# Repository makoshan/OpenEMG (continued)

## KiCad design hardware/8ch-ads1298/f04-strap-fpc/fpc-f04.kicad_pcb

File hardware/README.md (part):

# OpenEMG 模块化硬件家族总览（2ch / 8ch / 16ch 共用主控与壳体）

**当前下单主板**　[OpenEMG MAIN V1.0B 定版](main-v1.0b/)（2026-11-24）。4 层，首批已下单，实物验证待完成。

**配套腕带**　[OpenEMG WB v0.1 八节电极表带](wb-v0.1/)已机械定版，提供可编辑模型、打印文件和逐缝弯曲检查，待首件实测。

> [!IMPORTANT]
> **人工审核准备下单 vs AI 生成未下单（下单前必读）**
> - **经人工硬件工程师设计并逐脚审核通过、准备下单的 v0.01 双板**：[`16ch-afe-hirose-1mm-1nf/`](16ch-afe-hirose-1mm-1nf/)（`OpenEMG v0.01` 双板：6 层 `C08B-U9` 主控板 + 带 32 路 `ESD401DPYR` 输入保护管的广濑 `1.0 mm` `1 nF` 4 层采集板，146 个贴片位号，已对照 TI `ADS1298` 数据手册与 `SBAU171D` 逐脚审核通过，准备打样做离体台架首测）。
> - **其余 AI 生成设计（尚未人工审核 · 尚未下单）**：除历史 8 路台架开发板 [`8ch-ads1298/r01-bench/`](8ch-ads1298/r01-bench/) 已做过离体实板测试外，以下历史设计——包括 `16ch-u9-dual30/`（`22 pF` 穿戴派生版）、`16ch-afe-xunpu-2mm-1nf/`、`16ch-c08b-round/`（双 34 针 `D20/R4U6`）、`8ch-ads1298/afe-d20*-8ch/`、`2ch-ads1292/`、全部柔性电极软板（FPC）及全部 3D 打印外壳——均为 AI 生成参考设计，**尚未经人工工程师逐板审核，也尚未下单打样**。

**AI 结构与叠板探索 · 新版 16 通道小型化派生双板（双 30P 四层软板 + `9.60 mm` 超薄圆润手表壳，DRC 0 / 飞线 0，AI 生成未下单）**　[U9 圆角 6 层 `0.80 mm` 双核主控 `OpenEMG-C08B-Mainboard-Rev0.01`、超薄双 30P 4 层 `0.80 mm` 采集板 `AFE-30P`、双 30P 四层保护软板 `strap-fpc-30p` 与圆润无外露螺丝手表壳 `enclosure-u9-watch`](16ch-u9-dual30/) 使用东侧 20 芯反序排线直连，已完成：① 主控 `Rev0.01` 恢复 `26.64 × 20.90 mm` 原矩形电池窗（东梁宽 `2.76 mm`）、同步 6 层 `0.80 mm` 真实叠层、去掉中央 `DEBUG` 线框并整洁重排丝印、32MHz 晶振泪滴与 `BUTTON_N` 飞线清零；② `AFE-30P` 升级 `1.00 mm` 超薄上下双触点 30P 座（`C324727`）、`43.10 × 36.50 mm` 四角 `R1.80` 圆角与 `0.80 mm` 四层板厚、`FPC2.17/18` 交叉修正、`ADS1298` `RESV1=GND` 修正、32 颗共模电容空贴 DNP（钢网 64 孔全剥离）+ 16 颗 `22 pF` 差分电容保 CMRR、`C10=1 µF` 飞跨电容、`Inner2` 北数字 `GND`/南模拟 `AGND` 分岛及晶振下完整参考地；③ 配套 `32×100 kΩ + 2×200 kΩ` 贴肤限流双 30P 四层软板及 `46.80 × 40.00 × 9.60 mm` 超薄圆润手表壳（最小壁厚 `0.85 mm`，23 对三维布尔 `0.000 mm³` 零干涉）。下文 `D20 / R4U6 / 8ch / 2ch` 属于双 34 针及入门参考系列，完整保留供对照复刻。

本目录收录 OpenEMG 全系硬件的 **KiCad 10 原生工程**、**嘉立创 EDA 专业版（`.epro2` / `.epcb2`）工程**、**生产制造包（Gerber / BOM / CPL / IPC-D-356，全系 17 套直接上传包清单与 SHA-256 核对见 [ORDER-MATRIX.md](ORDER-MATRIX.md)）** 与 **3D 打印圆润外壳（`build123d` Python + STEP/STL/GLB）**，统一按 **[CERN-OHL-S-2.0](../LICENSE-HARDWARE)** 强互惠开源硬件协议发布。

最新工程师版见 [U9 主控与 D2 双 34P 采集板开发稿](u9-d2/README.md)。采集板正在重布线。

### 三维光追渲染预览（[`renders/`](renders/)，基于源工程一键复现，非实物照片）

> **边界说明**：以下 8 组 16 张图片均为 Blender Cycles 光追设计预览（哑光黑阻焊 + `#c8964a` 沉金焊盘 + 工程高透壳示意），不代表制造或人体佩戴验收；套件收纳图为模块化开源复刻防静电 EVA 收纳示意，非商业零售包装。复现脚本见 [`renders/README.md`](renders/README.md)。

| 类别 | 正交俯视（Top） | 透视斜视（Iso） |
|---|---|---|
| **1 · 成品总览**<br>左：16ch `C08B R13` 整表正反双姿态<br>右：2ch `ADS1292 R7` 一体盒正反双姿态 |  |  |
| **2 · 开源复刻套件收纳示意**<br>`C08B` 胶囊 + `8ch/2ch` 可换采集板 + `P44e` + `34P` 软板 + `Pod D1` |  |  |
| **3 · 三档叠板立体爆炸组装图**<br>左 `16ch R13` · 中 `8ch D20-8CH` · 右 `2ch R7` |  |  |
| **4 · 柔性电极表带系统**<br>`16ch D2` A/B 软板 + `8ch D2-8CH` 单片软板 + `0.8 mm` TPU 定位层 + `F04` 连续表带 |  |  |
| **5 · 贴肤镀金干电极微距**<br>`2ch` 板底六触点 + 外扣六孔底盖 `Cap D2` + `Pod D1` 单豆分解与 16 节织带阵列 |  |  |
| **6 · C08B 双板与胶囊叠装总览**<br>左：采集板 `D20` · 中：主控 `R4U6` · 右：叠装透视 |  |  |
| **7 · 下板：采集板 `D20`** |  |  |
| **8 · 上板：共用主控 `R4U6`** |  |  |

---

## A · 为什么 2 / 8 / 16 通道能共用同一个主控板与外壳家族？

三档穿戴采集板均采用完全相同的 **`43.10 × 36.50 mm`** 四层板框包络（同时提供配四角螺丝柱外壳 `R12` 的**圆孔版 `R4U6 / D20 / D20-8CH`**，以及配无螺丝抱柱外壳 `R13` 的**四角缺口版 `R4U6N / D20N / D20N-8CH`**，同档位两版 BOM/CPL 与走线 100% 一致），并统一使用东南角的 **20P `0.5 mm` 下接 FPC 座（`FH34SRJ-20S-0.5SH(50)`，立创 `C2802370`，开口均朝南）** 进行上下叠板互联，由 `firmware/c08b-bringup` 上电免跳线自动识别 `2ch / 8ch / 16ch`：

| 主控 `J_AFE` 脚号 | 共用主控 `R4U6` 网名 | 对应采集端脚号 (`21-k`) | `16ch D20` 网名 | `8ch D20` 单面贴网名 | `2ch ADS1292` 网名 | 兼容性结论 |
|---:|---|---:|---|---|---|---|
| `1, 2` | `3V3_AFE` | `20, 19` | `3V3` | `3V3` | `3V3` | ✓ 3.3V 供电直通 |
| `3` | `NC` | `18` | `ADS_CLKSEL`（板内下拉） | `ADS_CLKSEL`（板内下拉） | `NC` | ✓ 无冲突 |
| `4` | `ADS_DRDY_A` (`PA2`) | `17` | `ADS_DRDY_A` | `ADS_DRDY_A` | `ADS_DRDY_N` | ✓ 主片中断对齐 |
| `5` | `AFE_GPIO3` (`PA0`) | `16` | `AFE_GPIO3` | `AFE_GPIO3` | `NC` | ✓ 无冲突 |
| `6` | `DOUT_B` (`SPI1_MISO`) | `15` | `DOUT_B` | `DOUT_B` | `ADS_DOUT` | ✓ MISO 对齐 |
| `7, 9, 20` | `GND`（`8` 悬空） | `14, 12, 1` | `GND` | `GND` | `GND`（`13` 亦地） | ✓ 多点地回流对齐 |
| `10` | `AFE_SCLK` (`SPI1_SCK`) | `11` | `SCLK_B` | `SCLK_B` | `MCU_SCLK` | ✓ SPI 时钟对齐 |
| `11` | `AFE_CS_A` (`PB0`) | `10` | `ADS_CS_A` | `ADS_CS_A` | `ADS_CS_N` | ✓ 主片选对齐 |
| `12` | `AFE_START` (`PA3`) | `9` | `ADS_START` | `ADS_START` | `ADS_START` | ✓ 硬件同步启动对齐 |
| `13` | `NC` | `8` | `AFE_CLK_IN`（板载晶振） | `AFE_CLK_IN`（板载晶振） | `NC`（内部时钟） | ✓ 无冲突 |
| `14` | `AFE_RESET` (`PA8`) | `7` | `ADS_RESET` | `ADS_RESET` | `NC` | ✓ `ADS1292` 复位并入 `PWDN` |
| `15` | `AFE_PWDN` (`PA1`) | `6` | `ADS_PWDN` | `ADS_PWDN` | `MCU_PWDN` | ✓ 硬件掉电/复位对齐 |
| `16` | `AFE_DIN` (`SPI1_MOSI`) | `5` | `DIN_B` | `DIN_B` | `ADS_DIN` | ✓ MOSI 对齐 |
| `17` | `AFE_CS_B` (`PB1`) | `4` | `ADS_CS_B` | 空贴 `V4_U2` | `NC` | ✓ 2ch/8ch 悬空安全 |
| `18` | `AFE_DRDY_B` (`PA4`) | `3` | `ADS_DRDY_B` | 空贴 `V4_U2` | `AVDD_SENSE`（串 `100kΩ`） | ✓ 16ch 从片中断 / 2ch 读 3.0V 模拟电 |
| `19` | `NC`（`P44e` 上为 `5V`） | `2` | `NC` | `NC` | `XIAO_5V`（`10kΩ` 下拉） | ✓ 接 `R4U6` 时由主控切断 `3V3_AFE` 互锁；接 `P44e` 时驱动 `Q1` 互锁 |

### 机械坐标对位说明（板中心 `(0, 0)` 口径）
- **主控 `R4U6` 底面 `J_AFE`**：焊盘中心群 `(+14.34, -10.50) mm`（排线插口基准 `-11.75 mm`）
- **`8ch / 16ch D20` 顶面 `J_AFE`**：焊盘中心群 `(+14.34, -10.50) mm`（插口基准 `-11.75 mm`，与 `R4U6` **`0.00 mm` 完全正对**，短 U 形排线直连）
- **`2ch ADS1292` 顶面 `J2`**：`(+12.00, -11.40) mm`（与入门上层板 `P44e` `0.00 mm` 正对；若改配 `R4U6` 主控叠装，横向仅偏 **`2.34 mm`**，选用约 `25 mm` 长的 0.5 mm 20P 软排线微斜过渡即可）。

---

## B · 嘉立创 EDA 专业版工程文件（`.epro2` / `.epcb2`）快速索引

直接在**嘉立创 EDA 专业版（客户端 V2.2+ / 网页版）**选择「文件 → 导入 → 嘉立创EDA专业版」即可打开带完整原理图、多层 PCB 与 3D 预览的工程：

| 档位与用途 | 工程文件路径 | 说明 |
|---|---|---|
| **16ch `v0.01` 双板合并工程 + 广濑 `1.0 mm` `1 nF` 台架采集板 + 配套表带软板（A5＋B1）** | `16ch-afe-hirose-1mm-1nf/OpenEMG_v0.01_DualBoard.epro2`<br>`16ch-afe-hirose-1mm-1nf/kicad/`<br>`16ch-afe-hirose-1mm-1nf/strap-fpc-a5b1/OpenEMG_v0.01_Strap_FPC_A5B1.epro2`<br>`16ch-afe-xunpu-2mm-1nf/AFE-30P.epro2` | **2026-11-15 人工工程师逐脚审核定版双板工程**，采集板 D101–D132 共 32 颗 ESD401、146 个贴片位号（`01 主控板` + `02 采集板` 四角 `R1.80` 圆角、现货 `0603 R4=104kΩ C861070`、广濑 `1.0 mm` 双 30P + `1 nF` 差分网络，含同步单板 Gerber/BOM/CPL 及 1:1 导出的 KiCad 8 原生双板与九页原理图 `kicad/`）；配套 `strap-fpc-a5b1/` 双层 30P 表带软板（盒底 A5＋B1 六柱，已投单待实物试装）；附 AI 派生讯普 `2.0 mm` 对照版（未下单） |
| **16ch 6 层圆角主控 `Rev0.01` + 超薄双 30P `22 pF` 穿戴派生版（AI 生成 · 未下单）** | `16ch-u9-dual30/OpenEMG-C08B-Mainboard-Rev0.01.epro2`<br>`16ch-u9-dual30/AFE-30P.epro2` | AI 结构与叠板派生参考：6 层 `OpenEMG-C08B-Mainboard-Rev0.01` + 4 层 `0.80 mm` 圆角 `R1.80` 超薄双 30P（`C324727`）`AFE-30P`（`22 pF` 差分网络，含 `fab-mcu-u9/`、`fab-afe-30p/` 与 KiCad 四层软板 `strap-fpc-30p/`，尚未人工审核、尚未下单） |
| **16ch 圆孔全套汇总（配 `R12` 壳）** | `16ch-c08b-round/jlc-eda/C08B-全套汇总-主控R4U6-采集D20.epro2` | 同时包含 `R4U6` 主控板、双面 `D20` 采集板与双软板原理图 + 四层 PCB |
| **16ch 缺口全套汇总（配 `R13` 壳）** | `16ch-c08b-round/jlc-eda/C08B-全套汇总-主控R4U6N-采集D20N.epro2` | 同时包含四角缺口主控 `R4U6N`、双面缺口采集板 `D20N` 与双软板原理图 + 四层 PCB |
| **16ch 采集板独立工程（圆孔 / 缺口）** | `16ch-c08b-round/jlc-eda/C08B-AFE采集板-D20-原理图+PCB+3D.epro2`<br>`16ch-c08b-round/jlc-eda/C08B-AFE采集板-D20N-缺口-原理图+PCB+3D.epro2` | 16ch 双面采集板单板工程（圆孔版与四角缺口版） |
| **8ch 纯单面圆孔全套汇总（配 `R12` 壳）** | `8ch-ads1298/afe-d20-8ch/jlc-eda/C08B-8ch全套汇总-主控R4U6-采集D20-8CH单面.epro2`<br>[11 页全套 PDF](8ch-ads1298/afe-d20-8ch/views/schematic.pdf) · [34P/20P 逐针核对表](8ch-ads1298/afe-d20-8ch/PINOUT-AND-REVIEW.md) | 同时包含 `R4U6` 主控、纯单面 `D20-8CH` 采集板与单片 4 层软板 `D2-8CH` + **11 页原理图（含 P1 整机框图、P2 电源树）** |
| **8ch 纯单面缺口全套汇总（配 `R13` 壳）** | `8ch-ads1298/afe-d20n-8ch/jlc-eda/C08B-8ch全套汇总-主控R4U6N-采集D20N-8CH单面.epro2` | 同时包含 `R4U6N` 缺口主控、纯单面缺口 `D20N-8CH` 采集板与单片软板 `D2-8CH` + 9 页原理图 |
| **8ch 纯单面采集板独立工程（圆孔 / 缺口）** | `8ch-ads1298/afe-d20-8ch/jlc-eda/C08B-AFE采集板-D20-8CH-单面8路-原理图+PCB+3D.epro2`<br>[6 页采集板 PDF](8ch-ads1298/afe-d20-8ch/views/afe-schematic.pdf)<br>`8ch-ads1298/afe-d20n-8ch/jlc-eda/C08B-AFE采集板-D20N-8CH-缺口单面8路-原理图+PCB+3D.epro2` | 纯单面 8 路采集板（正面 76 颗贴片，背面 0 器件绿油绝缘；圆孔版含 **6 页原理图**与[排线朝向图](8ch-ads1298/afe-d20-8ch/views/d20-8ch-wiring-orientation.svg)） |
| **8ch 单片 4 层表带软板 `D2-8CH`** | `8ch-ads1298/strap-fpc-d2-8ch/jlc-eda/C08B-表带软板-D2-8CH单片.epro2` | 单片 4 层 34P 软板（胶囊底双辅助 `200k` 串阻 + 6 窗 `0.20 mm` PI 垫片复用现成底盖） |
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
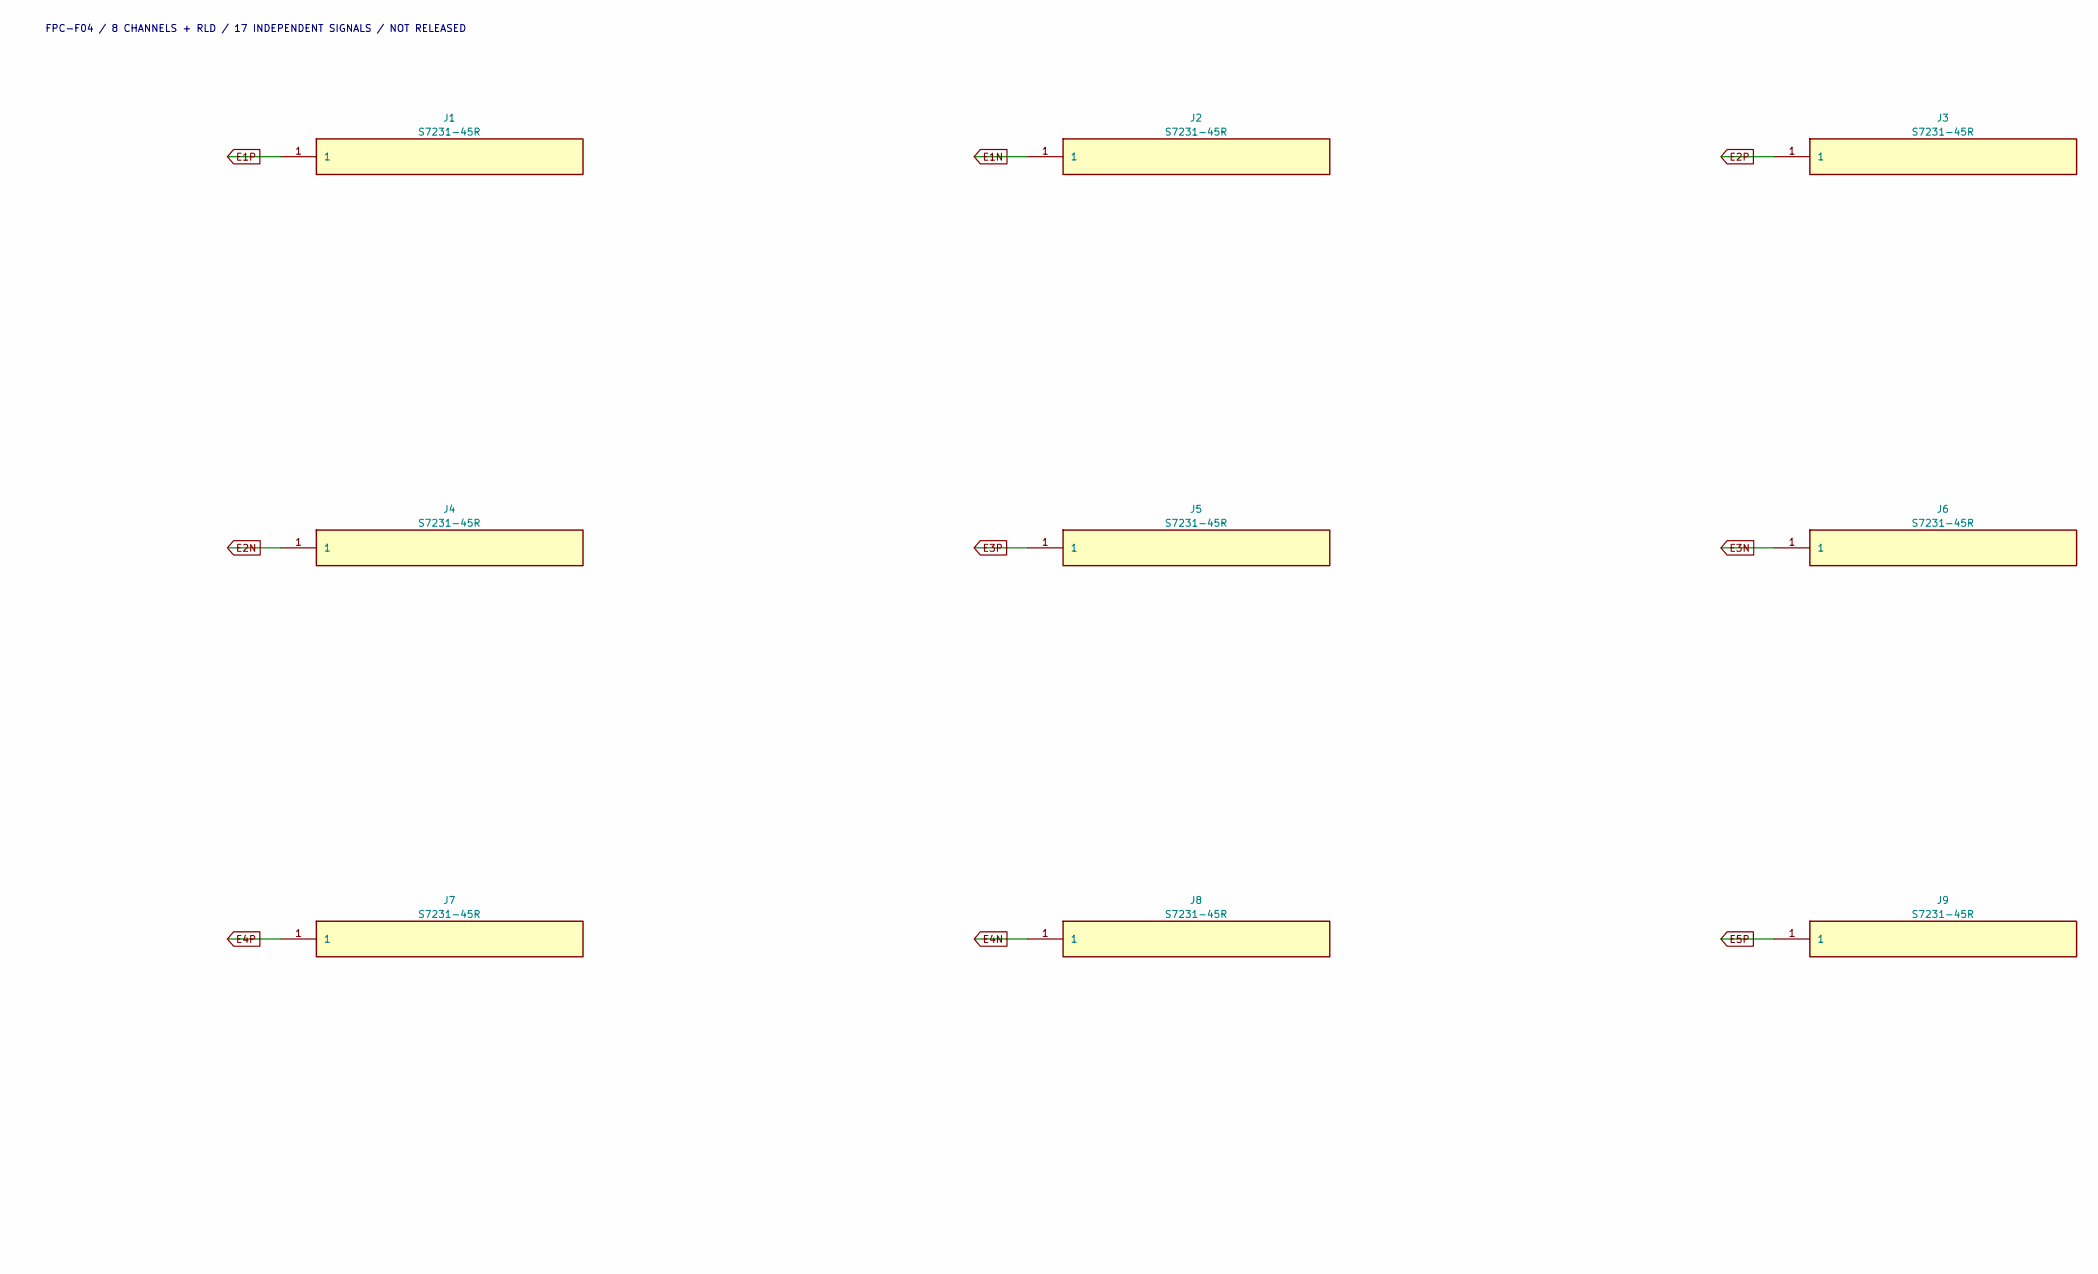
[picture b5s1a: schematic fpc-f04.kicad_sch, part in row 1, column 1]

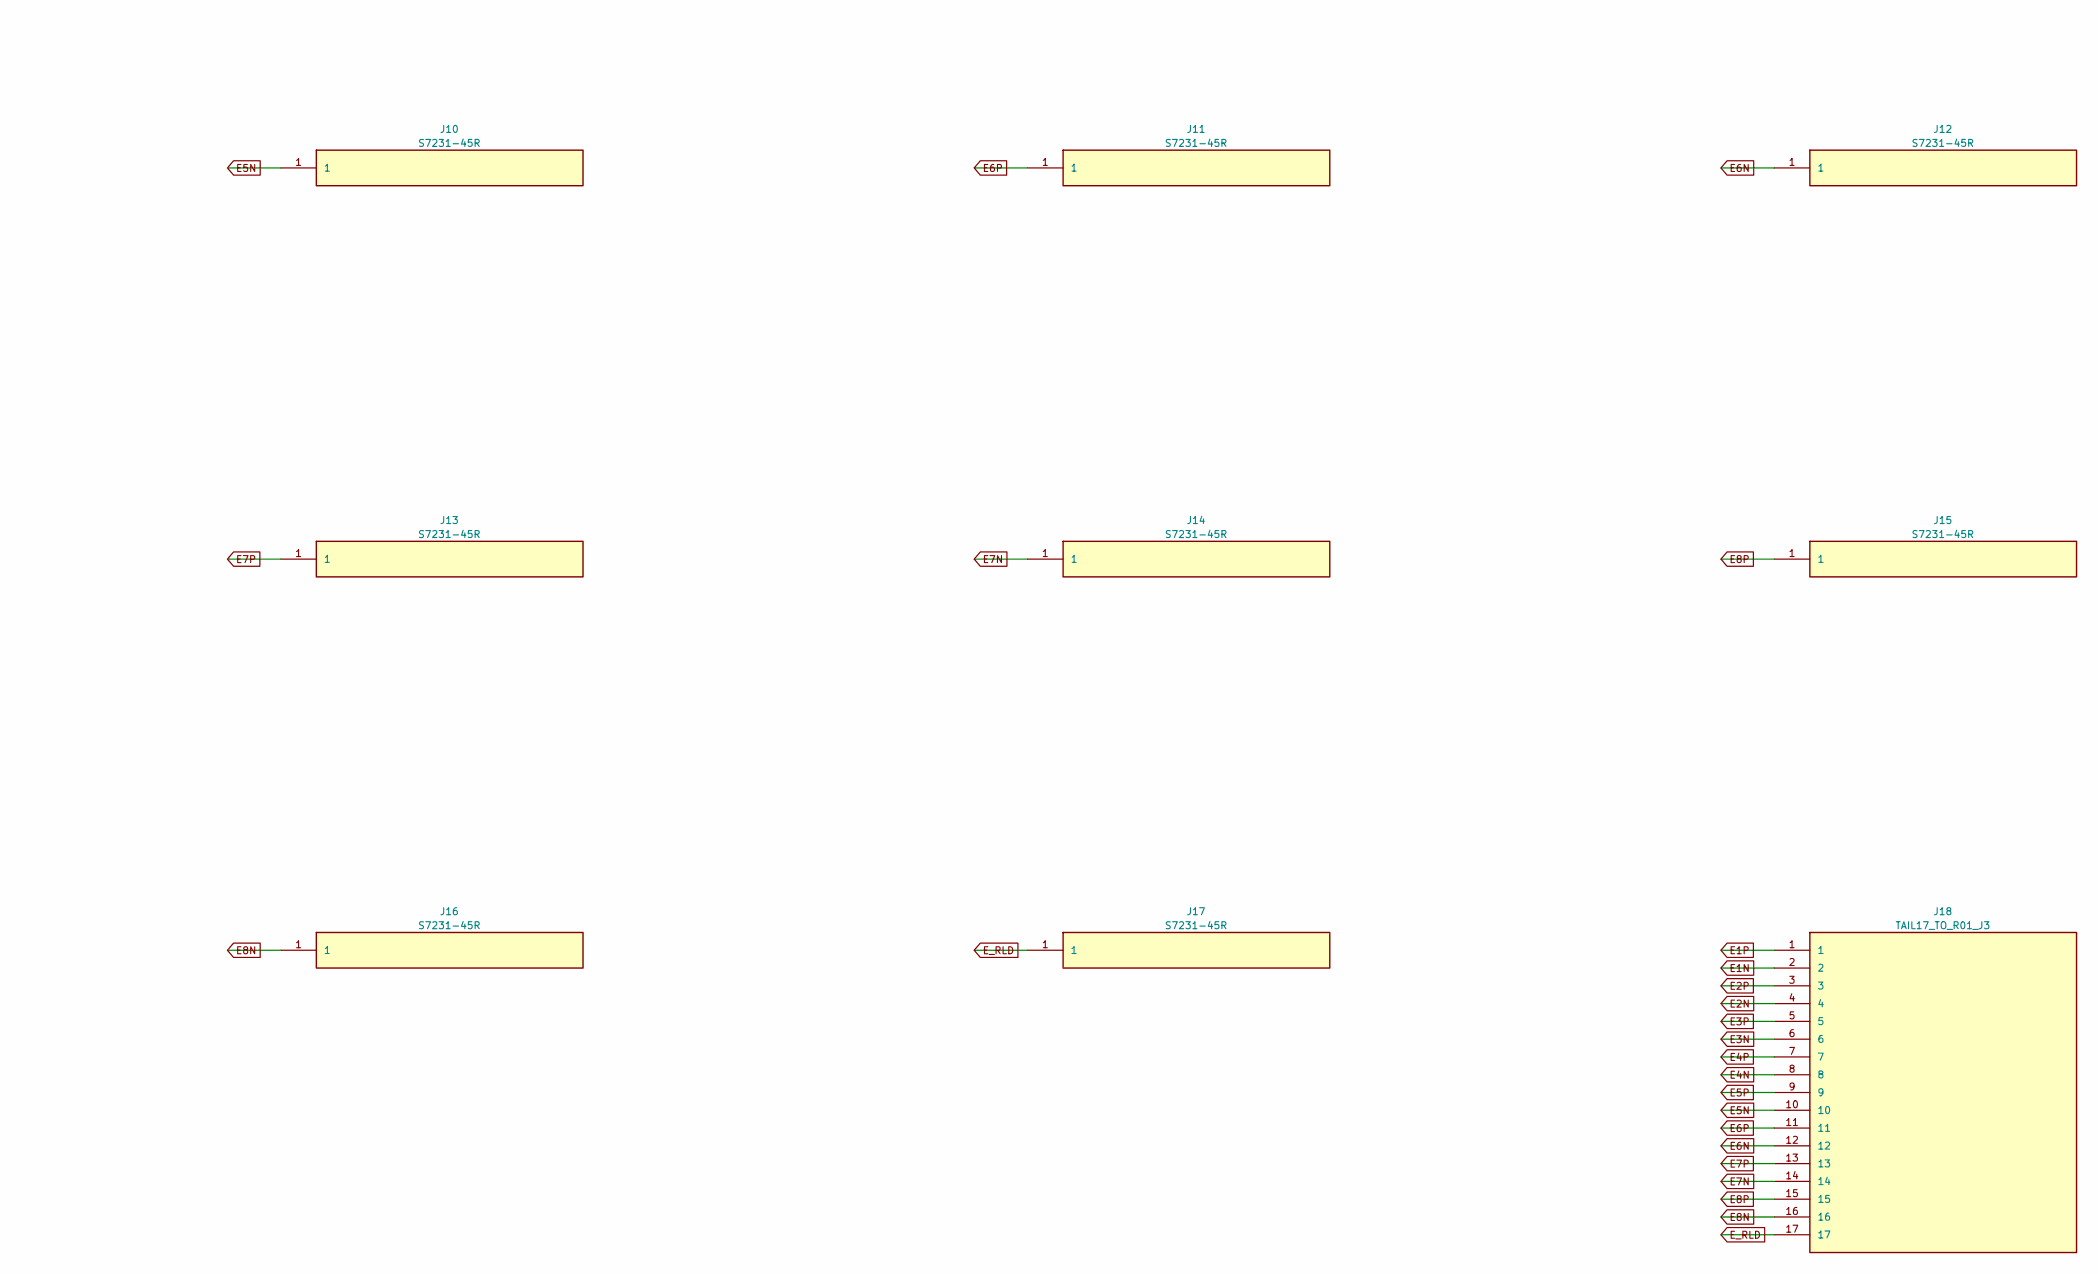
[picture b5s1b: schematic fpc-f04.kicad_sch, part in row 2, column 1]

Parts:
J1, J2, J3, J4, J5, J6, J7, J8, J9, J10, J11, J12, J13, J14, J15, J16, J17: S7231-45R; S7231
J18: TAIL17_TO_R01_J3; TAIL17

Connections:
E1N: J2.1, J18.2
E1P: J1.1, J18.1
E2N: J4.1, J18.4
E2P: J3.1, J18.3
E3N: J6.1, J18.6
E3P: J5.1, J18.5
E4N: J8.1, J18.8
E4P: J7.1, J18.7
E5N: J10.1, J18.10
E5P: J9.1, J18.9
E6N: J12.1, J18.12
E6P: J11.1, J18.11
E7N: J14.1, J18.14
E7P: J13.1, J18.13
E8N: J16.1, J18.16
E8P: J15.1, J18.15
E_RLD: J17.1, J18.17

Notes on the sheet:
FPC-F04 / 8 CHANNELS + RLD / 17 INDEPENDENT SIGNALS / NOT RELEASED

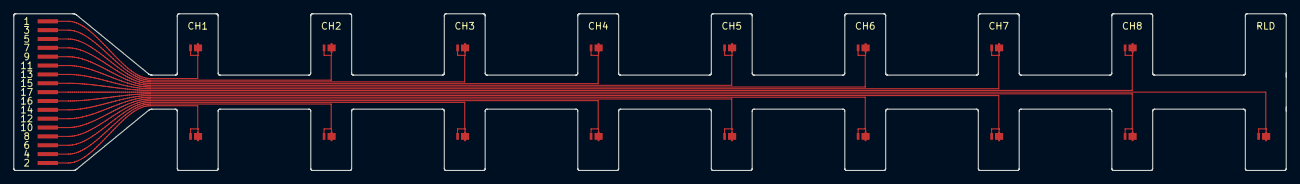
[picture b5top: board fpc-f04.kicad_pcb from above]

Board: 2 copper layers, 186.8 x 23.0 mm, 18 parts (0 on the bottom side), 17 nets.

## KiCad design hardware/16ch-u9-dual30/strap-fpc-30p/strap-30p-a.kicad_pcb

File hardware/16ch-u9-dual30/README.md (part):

# 16 通道小型化旗舰：U9 圆角 6 层主控（`Rev0.01`）+ 超薄双 30 针采集板 + 四层保护软板 + 超薄圆润手表壳（2026-11-14 开源定版）

本目录收录 `OpenEMG-C08B-Mainboard-Rev0.01`（6 层 `0.80 mm` 圆角双核主控，原矩形 `26.64 × 20.90 mm` 电池窗、去中央 DEBUG 框洁净丝印版）与 `AFE-30P`（4 层 `0.80 mm` 圆角超薄双 30 针 16 路采集板）配对工程、嘉立创直接上传制造包（单板与 `70.20 × 70.20 mm` 工艺边 Gerber、SMT BOM、192 颗逐脚拟合校核 CPL、极性图）、满载器件整板 STEP、双 30P 四层保护表带软板（`strap-fpc-30p/`）以及 `9.60 mm` 超薄圆润无外露螺丝手表壳（`enclosure-u9-watch/`，同时保留台架候选壳 `case-30p/`），按 [CERN-OHL-S-2.0](../../LICENSE-HARDWARE) 发布。

## 文件清单

| 路径 | 说明 |
|---|---|
| `OpenEMG-C08B-Mainboard-Rev0.01.epro2` / `mcu-u9-3d.step` | 6 层 `0.80 mm` 主控板（`STM32L432KCU6` `U7` + `nRF52840-QFAA` `U8`，`43.10 × 36.50 mm` 四角 `R=1.80 mm` + `26.64 × 20.90 mm` 原矩形电池开窗 + 去中央 DEBUG 框洁净丝印）及满载 588 实体 STEP |
| `AFE-30P.epro` / `AFE-30P.epro2` / `afe-30p-3d.step` | 4 层 `0.80 mm` 16 路圆角采集板（双 `ADS1298IPAGR` `U1/U2` + 双 `1.00 mm` 超薄上下双面触点 30P 座 `FPC1/FPC3` `C324727` + 20P 双面触点座 `FPC2` `Molex 503480-2000`）及满载 306 实体 STEP（已剔除 32 颗 DNP 共模电容占位块） |
| `20针接口.csv` | `MCU-U9 FPC1`（1..20）↔ `AFE-30P FPC2`（20..1）逐脚网络锁定表 |
| `fab-mcu-u9/OpenEMG-C08B-Mainboard-Rev0.01-Gerber.zip` | 主控 `Rev0.01` 6 层单板 Gerber（`GTL, G1..G4, GBL` + `GKO` + `PTH/NPTH`，已剔除 14 处手焊/DNP 钢网开窗，无中央 DEBUG 线框） |
| `fab-mcu-u9/OpenEMG-C08B-Mainboard-Rev0.01-panel702-Gerber.zip` | 主控 `Rev0.01` 自带 `70.20 × 70.20 mm` 工艺边（`2.0 mm` 铣槽 + 四边断口连接筋）一拼一 Gerber |
| `fab-mcu-u9/jlc_smt_bom.csv` / `jlc_smt_cpl.csv` | 主控 `Rev0.01` 嘉立创 SMT 物料清单与贴片坐标（45 种 / 110 颗：Top 42 + Bottom 68，按平台默认「AD 等其他」逐脚拟合） |
| `fab-mcu-u9/orientation.csv` / `polarity-*.png` | 主控 `Rev0.01` 有极性/多引脚器件 1 脚与阴极坐标核对表及顶/底层粉点核对图 |
| `fab-afe-30p/Gerber_AFE-30P.zip` | `AFE-30P` 4 层 `0.80 mm` `R=1.80 mm` 圆角单板 Gerber（`GTL, G1, G2, GBL` + `GKO` + `PTH`；`GTP/GBP` 已剥离全部 32 颗 DNP 共模电容共 64 个钢网开孔） |
| `fab-afe-30p/Gerber_AFE-30P-panel702.zip` | `AFE-30P` 自带 `70.20 × 70.20 mm` 工艺边（同心 `R1.80/R3.80` 圆角 `2.0 mm` 铣槽 + 6 处断口连接筋，完全避开南侧双 30P 与东侧 20P 插口）一拼一 Gerber |
| `fab-afe-30p/jlc_smt_bom.csv` / `jlc_smt_cpl.csv` | `AFE-30P` 嘉立创 SMT 物料清单与贴片坐标（22 种 / 82 颗：Top 48 + Bottom 34，100% 现货 `C` 料号，含 `C324727`、`R4=C2984407`、`C10=C52923` 1µF 与 16×`22pF` `C76924`，按平台默认「AD 等其他」逐脚拟合） |
| `fab-afe-30p/orientation.csv` / `polarity-*.png` | `AFE-30P` 有极性/多引脚器件 1 脚与阴极坐标核对表及顶/底层粉点核对图 |
| `strap-fpc-30p/` | 适配 `FPC1/FPC3` 横向错位 `1.524 mm` 的 **12+2+2 双极四层柔性表带软板**（`strap-30p-a` + `strap-30p-b`）：自带 `32 × 100 kΩ`（`C25741`）采样限流串阻与 `2 × 200 kΩ`（`C25811`）偏置串阻（叠加板上 `15 kΩ` / `392 kΩ` 后总串联阻抗 `115 kΩ` / `592 kΩ`），含 28 项门禁 `check.py`、满载 3D STEP 与 `fab/` 生产包 |
| `enclosure-u9-watch/` | **穿戴主力超薄圆润无外露螺丝手表壳**（主体净高 **`46.80 × 40.00 × 9.60 mm`**，`≤ 9.70 mm`；含外扣底盖不计铜凸 `10.806 mm`，含 `1.20 mm` 电极尖端总包络 `12.006 mm`；全壳最小壁厚 **`0.85 mm ≥ 0.80 mm`**）：内柱盲孔 `4 × M1.4` 紧固 + `cap_bottom` 卡扣遮蔽，经 `fit_3d_check.py` 核验满载双板/电芯/双软板共 **23 对三维布尔交叠 `0.000 mm³`** 及 9 项正反例对照 |
| `case-30p/` | 离体台架候选盒总装 STEP（`Case.step`、`Lid.step`、`assembly.step`）、`19.67 × 26.59 × 2.78 mm` 电芯干涉报告 `checks.json` 与装配图 |
| `verify_interface.py` / `SHA256SUMS` | 20P 逐脚对账、双核 39 信号脚固件兼容、60 脚双 30P 映射、双板 `0.80 mm` 叠层、前端 RC/电荷泵修正与 0/64 DNP 钢网零残留、192 颗 CPL 逐脚拟合（含 4 项必败反例）、铺铜与全套 3D 总装自检脚本及 SHA-256 校验表 |

## 已修复的工程与制造问题（嘉立创 EDA 专业版 `4.1.93` 原生复核通过）

### 1. 主控板 `OpenEMG-C08B-Mainboard-Rev0.01`（6 层 `0.80 mm`，`43.10 × 36.50 mm`）
- **定版原矩形电池镂空窗、东梁强度恢复与 `0.80 mm` 真实叠层同步**：电池开窗 `a6b31685508e342e` 采用无阶梯纯矩形 **`26.638 × 20.900 mm`**（东侧梁宽恢复至 **`2.762 mm`**，完美容纳标准 `302025` 锂电池且与 `SCREW3` 孔留足边距），同步对齐 `Inner3/Inner4` 内电层镂空框并重铺全部 10 块铜皮（`10 POUR / 24 POURED`）；`LAYER_PHYS` 同步为真实 6 层 `0.80 mm`（`JLC06081H-3313`，`31.321 mil = 0.7956 mm`），导出 588 实体 `mcu-u9-3d.step` 使整表壳体净高降至 **`9.60 mm`**。
- **四角 `R=1.80 mm` 圆角板框、北边拉平与洁净丝印**：消除原版北边 `0.166 mm` 倾斜，统一四角圆弧与内电层退缩外框；板面升级 `OpenEMG 0.01` 标识、去掉顶面中央 `DEBUG` 线框并双列对齐背面位号丝印。
- **消除全部网络飞线与孤立铜皮**：将 `BUTTON_N` 走线 `aa2a5e4ee3874f57` 延伸至 `SW300.1` 焊盘中心 `324.087 mil`，移除 2 处孤立泪滴，西南角地过孔 `cc7fc0d843f8c411` 内移至 `-1303 mil`；原生 DRC **0 间距/几何/连接错误、0 飞线**。
- **原理图与 PCB 充电芯片同步**：`U17` 统一为 `LTC4054ES5-4.2#TRPBF`（`SOT-23-5`，立创 `C462648`）。
- **钢网防连锡处理**：单板与 `70.2 × 70.2 mm` 工艺边 Gerber 已自动剔除 `J301`、`JP701`、`D62`、`BT1`、`ANT1` 等 14 处手焊/空贴焊盘钢网开孔。

### 2. 采集板 `AFE-30P`（4 层 `0.80 mm`，`43.100 × 36.500 mm` 四角 `R=1.80 mm`）
- **小型化机械与超薄双触点连接器升级**：板框收为与主控同心的 **`43.100 × 36.500 mm` 四角 `R=1.800 mm` 圆角板框**，四层叠层设为 **`0.80 mm`（`JLC04081H-3313`）**；正反双面 30P 表带座 `FPC1 / FPC3` 由 `2.00 mm` 高下接座升级为 **`1.00 mm` 超薄上下双面触点广濑 `FH34SRJ-30S-0.5SH(50)`（立创 `C324727`）**（无需区分上下接金手指面）。
- **前端高阻干电极 RC 滤波修正（消除工频共模转差模与肌电通带衰减）**：配合四层软板 `strap-fpc-30p` 的 `100 kΩ` 贴肤限流电阻（每脚总串联电阻 `R_leg = 115 kΩ`），将 32 颗对地共模电容（`C55, C57..C71, C93..C108`）全部设为 **空贴 DNP** 并在单板/拼板 Gerber `GTP/GBP` 钢网中 100% 剥离其 64 个焊盘开孔（避免 `±5%` 容差把 50 Hz 共模干扰直接转成差模底噪，并将原 `115 kΩ × 564 pF → f_c = 2.45 kHz` 误削肌电高频的问题彻底修正），同时将 16 颗跨通道差分电容（`C72..C79, C109..C116`）由 `47 pF` 调整为 **`22 pF C0G`（`GRM0335C1H220JA01D`，立创 `C76924`）**，精确锁定纯差模抗混叠截止频率 $f_{c,\text{diff}} = \frac{1}{2\pi \cdot 230\,\text{k}\Omega \cdot 22\,\text{pF}} = 31.45\,\text{kHz}$。
- **`LM27762` 负压电荷泵飞跨电容修正**：依 TI `LM27762` 手册 §8.2.1.2.3 要求，将飞跨电容 `C10` 由 `10 µF` 修正为 **`1 µF X5R 0402`（`CL05A105KA5NQNC`，立创 `C52923`）**，消除启动浪涌电流与电荷泵开关纹波超标隐患。
- **20P 反序排线 `FPC2.17 / 18` 交叉修复**：`FPC2` 第 17 脚改接 `CS#2`（`U2.39`，对主控 `FPC1.4，AFE_CS_B`），第 18 脚改接 `DRDY2#`（`U2.47`，对主控 `FPC1.3，AFE_DRDY_B`），过孔 `e1998` 移至 `(1305, 792.3834) mil`。
- **双 `ADS1298` 第 31 脚 `RESV1` 修正为数字地 `GND`**：依 TI `ADS1298` 数据手册（`RESV1` 必须接 `DGND`），将原理图（`1.esch` `e95/e300`）与 PCB（`U1.31`、`U2.31` 及相连过孔/短线）从 `AGND` 改为 `GND`，消除原理图与 PCB 网表差异（`0 Netlist Error`）。
- **`Inner2` 北数字 `GND` / 南模拟 `AGND` 分岛与晶振完整参考地**：将 `Inner2`（`layer 16`）拆分为北侧数字区 `POUR e1678 (GND)` 与南侧模拟电极区 `POUR e1687 (AGND)`（避免数字返回电流耦合进高阻电极扇出区），移除 `2.048 MHz` 晶振 `X1` 正下方的禁止铺铜框 `REGION e1680` 为时钟提供完整 `GND` 参考平面，保留 `RULE 7` 直连（`connType=1`），并在 `LCEDA-Pro 4.1.93` 重建全部 15 块铺铜；原生 DRC **0 错误、0 飞线、0 网表不一致**。
- **补齐全部 SMT 立创现货料号**：补齐 `C1, C2`（`22uF` `0402` `C105226`）、`C4, C34`（`10uF` `0402` `C7472949`）并将负轨反馈电阻 `R4` 更新为现货 `105 kΩ ±0.1%`（`C2984407`），整板 22 种 / 82 颗贴片件 100% 具备有效现货 `C` 料号。

### 3. 嘉立创 SMT 贴片坐标（`jlc_smt_cpl.csv`）极性与背面镜像修正
- 嘉立创 SMT 下单页默认选中 **「AD,99SE,Allegro,PADS(宏)等其他」**（背面按封装先 `X` 取反再旋转 `Rotation` 角），而嘉立创 EDA 内部 `COMPONENT` 背面按 `Y` 取反旋转，二者在背面相差 **`180°`**。
- `fab-mcu-u9/jlc_smt_cpl.csv`（110 颗）与 `fab-afe-30p/jlc_smt_cpl.csv`（82 颗）共 **192 颗**贴片件已统一修正为嘉立创默认上传模式（顶层保持原角，底层加 `180°`），经 `verify_interface.py` 逐脚拟合校验（最大焊盘偏差 **`0.0000 mm`**；`U17`、`FPC1`、`U2`、`FPC3` 减回 `180°` 反例均报 `> 1.5 mm` 错位拦截）。
- **下单必读**：上传 `jlc_smt_cpl.csv` 时**保持平台默认的「AD,99SE,Allegro,PADS(宏)等其他」选项，切勿改选「嘉立创EDA」**；在 2D 预览页同时勾选顶层与底层，对照 `orientation.csv` 及 `polarity-top.png` / `polarity-bottom.png` 核对粉点。

## 20 芯反序排线与三维 U 形装配关系（含防混插短路告警）

- 电气映射：主控 `FPC1` 的第 $k$ 脚接采集板 `FPC2` 的第 $21-k$ 脚。主控 `19、20` 脚为受控 `3V3_AFE`，接采集板 `2、1` 脚（`+3.3V`）；主控第 `1` 脚为 `GND`，接采集板第 `20` 脚（`GND`）。完整逐脚映射见 [20 针接口表](20针接口.csv)。
- 三维叠板走线：主控 `Rev0.01` 底面 `FPC1`（开口朝东，第 `1` 脚在北、第 `20` 脚在南）与下层 `AFE-30P` 顶面 `FPC2`（开口朝东，第 `20` 脚在北、第 `1` 脚在南）均为 `Molex 503480-2000` 上下双面触点座且南北物理对齐；使用 **20 芯 `0.5 mm` A 型（同面）软排线**向外平折 U 形直插即可自然实现 `k ↔ 21−k` 连接。
- **严禁跨系列混插警告**：`OpenEMG-C08B-Mainboard-Rev0.01`（东侧 `FPC1.1=GND, 19/20=3V3_AFE`）**仅限与 `AFE-30P` 互连**；切勿与 `R4U6 / D20 / D20-8CH / ADS1292-2ch` 系列（南侧 `J_AFE.1/2=3V3_AFE, 20=GND`）混插 20P 排线，亦严禁台架 `1 ↔ 1` 直连，否则上电瞬间 `3V3_AFE` 直接对 `GND` 短路。

## 固件二进制兼容与烧录路径

主控 `Rev0.01` 的双核信号脚（`U7 STM32L432KCU6` 23+3 脚 + `U8 nRF52840-QFAA` 16 脚，由 `verify_interface.py`、`c08b-bringup/tools/pins_u9.py` 与 `c08b-stream/tools/pins.py --check-u9` 三重自动断言）可直接运行免改动的 [`firmware/c08b-bringup`](../../firmware/c08b-bringup/README.md) 与 [`firmware/c08b-stream`](../../firmware/c08b-stream/README.md) 固件镜像：其中运行信号脚分配与 `R4U6 / R4U6N` 完全一致，仅 `U7.31`（`PH3-BOOT0`）接 `L_BOOT0`（经 `R5` `10 kΩ` 下拉至 `GND`，固件配置为无上下拉高阻输入，`L432` 侧 `l432_vbus_present()` 恒读 `0`；USB 电气安全互锁由硬件 `VBUS → R703/R704 → Q3 → U4 → OE_N` 切断隔离器以及 `nRF52840` 侧 `U8.3 P0.01=VBUS_SENSE` / `U8.15 P0.17=OE_N` 完整执行，自检与采集流均正常通过）：
1. **`nRF52840`（`U8`）**：通过顶面 `J301` 焊盘（`SWDIO / SWDCLK / GND / 3V3`）经 SWD 探针烧写 `nrf.hex` / `nrf_s140.hex`。
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
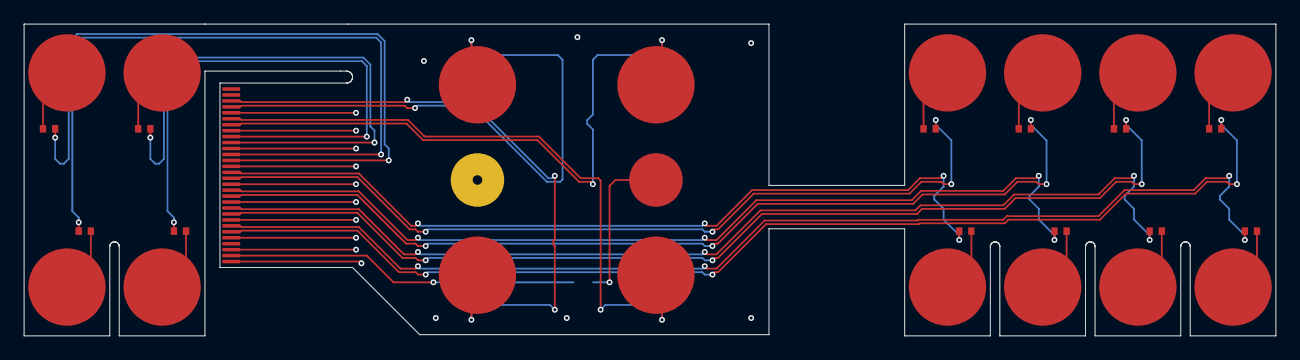
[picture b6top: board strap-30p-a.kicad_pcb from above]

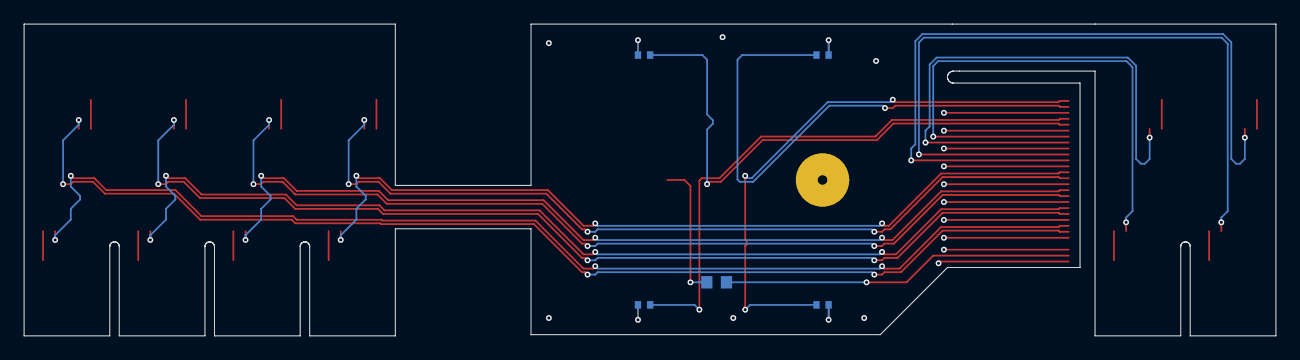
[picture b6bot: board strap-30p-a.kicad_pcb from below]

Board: 4 copper layers, 105.2 x 26.2 mm, 36 parts (5 on the bottom side), 35 nets.

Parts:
E1N, E1P, E2N, E2P, E3N, E3P, E4N, E4P, E5N, E5P, E6N, E6P, E7N, E7P, E8N, E8P: 贴肤焊盘（焊 Φ6×2.0 镀金铜片）; CONTACT_SMD_D6.5
EB1: 贴肤焊盘（焊方形 3×3×2 镀金铜片）; CONTACT_SMD_D6.5
EB2A: REF 贴肤焊盘（焊方形 3×3×2，孔内灌锡对焊 B 片 EB2）; CONTACT_D1.8
R1, R2, R3, R4, R5, R6, R7, R8, R9, R10, R11, R12, R13, R14, R15, R16: 100k; R0402
R33: 200k; R0603
TAIL_A: AFE-30P FPC1; FPC30_P0.5_TAIL

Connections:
AGND: TAIL_A.5, TAIL_A.8, TAIL_A.11, TAIL_A.14, TAIL_A.17, TAIL_A.20, TAIL_A.23, TAIL_A.26, TAIL_A.28, TAIL_A.30
BIAS_DRV1: R33.1, TAIL_A.29
BIAS_DRV1_E: EB1.1, R33.2
CH1_N: R2.1, TAIL_A.4
CH1_N_E: E1N.1, R2.2
CH1_P: R1.1, TAIL_A.3
CH1_P_E: E1P.1, R1.2
CH2_N: R4.1, TAIL_A.7
CH2_N_E: E2N.1, R4.2
CH2_P: R3.1, TAIL_A.6
CH2_P_E: E2P.1, R3.2
CH3_N: R6.1, TAIL_A.10
CH3_N_E: E3N.1, R6.2
CH3_P: R5.1, TAIL_A.9
CH3_P_E: E3P.1, R5.2
CH4_N: R8.1, TAIL_A.13
CH4_N_E: E4N.1, R8.2
CH4_P: R7.1, TAIL_A.12
CH4_P_E: E4P.1, R7.2
CH5_N: R10.1, TAIL_A.16
CH5_N_E: E5N.1, R10.2
CH5_P: R9.1, TAIL_A.15
CH5_P_E: E5P.1, R9.2
CH6_N: R12.1, TAIL_A.19
CH6_N_E: E6N.1, R12.2
CH6_P: R11.1, TAIL_A.18
CH6_P_E: E6P.1, R11.2
CH7_N: R14.1, TAIL_A.22
CH7_N_E: E7N.1, R14.2
CH7_P: R13.1, TAIL_A.21
CH7_P_E: E7P.1, R13.2
CH8_N: R16.1, TAIL_A.25
CH8_N_E: E8N.1, R16.2
CH8_P: R15.1, TAIL_A.24
CH8_P_E: E8P.1, R15.2

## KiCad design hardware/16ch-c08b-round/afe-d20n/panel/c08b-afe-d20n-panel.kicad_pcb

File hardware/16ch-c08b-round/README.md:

# 16 通道旗舰圆角上下叠板（`16ch-c08b-round`）

上层配共用主控 [`../common-mainboard/mainboard-r4u6/`](../common-mainboard/mainboard-r4u6/)（圆孔）或 [`../common-mainboard/mainboard-r4u6n/`](../common-mainboard/mainboard-r4u6n/)（四角缺口），下层为本目录的双面双 `ADS1298` 16 通道采集板 `afe-d20/`（圆孔）或 `afe-d20n/`（四角缺口），外接 34P 四层柔性表带软板，分别装入 [`../enclosure-46x40/c08b-shell-r12/`](../enclosure-46x40/c08b-shell-r12/)（螺丝壳）或 [`../enclosure-46x40/c08b-shell-r13-notch/`](../enclosure-46x40/c08b-shell-r13-notch/)（无螺丝抱柱壳）。

| 采集板 `D20` 正交俯视（渲染预览） | 采集板 `D20` 透视斜视（渲染预览） |
|---|---|
|  |  |

| 34P 双片柔性软板与 `0.8 mm` TPU 定位层（三维光追设计预览，非实物照片，不代表制造或人体佩戴验收通过） | 外扣六孔底盖与 `Pod D1` 穿带式双极干电极（三维光追设计预览，非实物照片，不代表制造或人体佩戴验收通过） |
|---|---|
|  |  |

## 目录结构

- `afe-d20/`：**圆孔版（配 `R12` 螺丝壳）** KiCad 10 原生工程（自带 `libs/` 封装库与 `assembly/models/FPC2-fh34.step`，DRC 0 违规 / 0 未连）、满载 127 颗器件的整板三维模型 **`c08b-afe-d20-3d.step`**、邮票孔拼板 Gerber、双面 SMT BOM/CPL。
- `afe-d20n/`：**四角缺口版（配 `R13` 无螺丝壳）** KiCad 10 原生工程（BOM/CPL 与 `afe-d20` 逐字节一致，仅四角改为无螺丝抱柱缺口）、满载 127 颗器件的整板三维模型 **`c08b-afe-d20n-3d.step`**、邮票孔拼板 `panel/c08b-afe-d20n-panel-gerber.zip`。
- `schematics-afe/`：采集板 4 页 SVG 原理图及 529 脚逐脚对板校验脚本 `check_all.py`。
- `jlc-eda/`：**嘉立创 EDA 专业版完整工程**（圆孔版 `C08B-全套汇总-主控R4U6-采集D20.epro2` / `C08B-AFE采集板-D20-原理图+PCB+3D.epro2`，以及四角缺口版 `C08B-全套汇总-主控R4U6N-采集D20N.epro2` / `C08B-AFE采集板-D20N-缺口-原理图+PCB+3D.epro2`）。
- `strap-fpc-d2/`：配合现成 `25 mm` 表带贴装的 12+2+2 四层 34P 双片表带电极软板（含满载 `strap-{a,b}-3d.step` 与 `fit_3d_check.py` 叠层 `0.0 mm³` 零干涉证明、`fab/` 嘉立创 FPC+SMT 直传包 `strap-a-gerber.zip` `b7aa2a09` / `strap-b-gerber.zip` `43175156`）及 `0.8 mm` TPU 开孔定位层（`tpu-layer-d2/`，含 `.step`/`.stl`/`.3mf`）。
- `strap-fpc-r15/`：配合一体成型 TPU 表带入口（`c08b-shell-r12` / `c08b-shell-r13-notch`）的 34P 四层双片软板（含 `strap-{a,b}-3d.step`）。
- `pod-d1/`：穿在现成 `25 mm` 魔术贴表带上的独立 TPU95A 电极豆方案（`pod_d1.step`、16 连条 `pod_strip_d1.{step,stl}` 与 Bambu X2D 切片包 `.3mf`）。
- `firmware-guide.md`：双片 `ADS1298` 同源 `2.048 MHz` 同步采样状态机与寄存器配置手册。

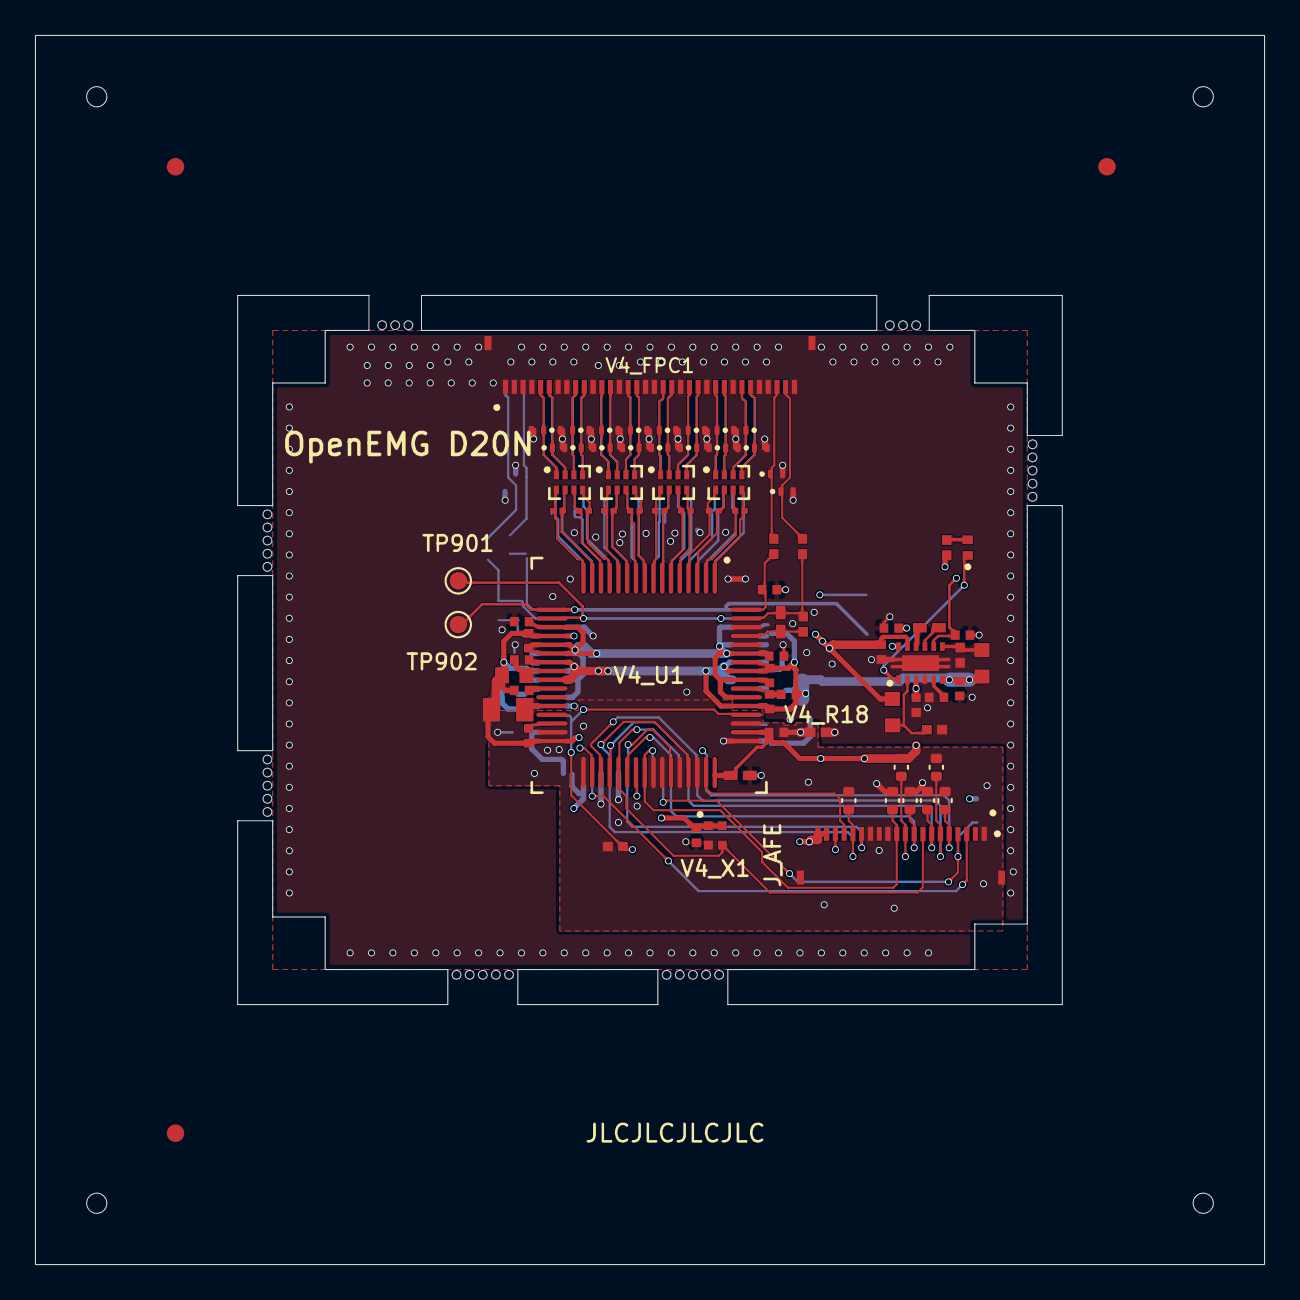
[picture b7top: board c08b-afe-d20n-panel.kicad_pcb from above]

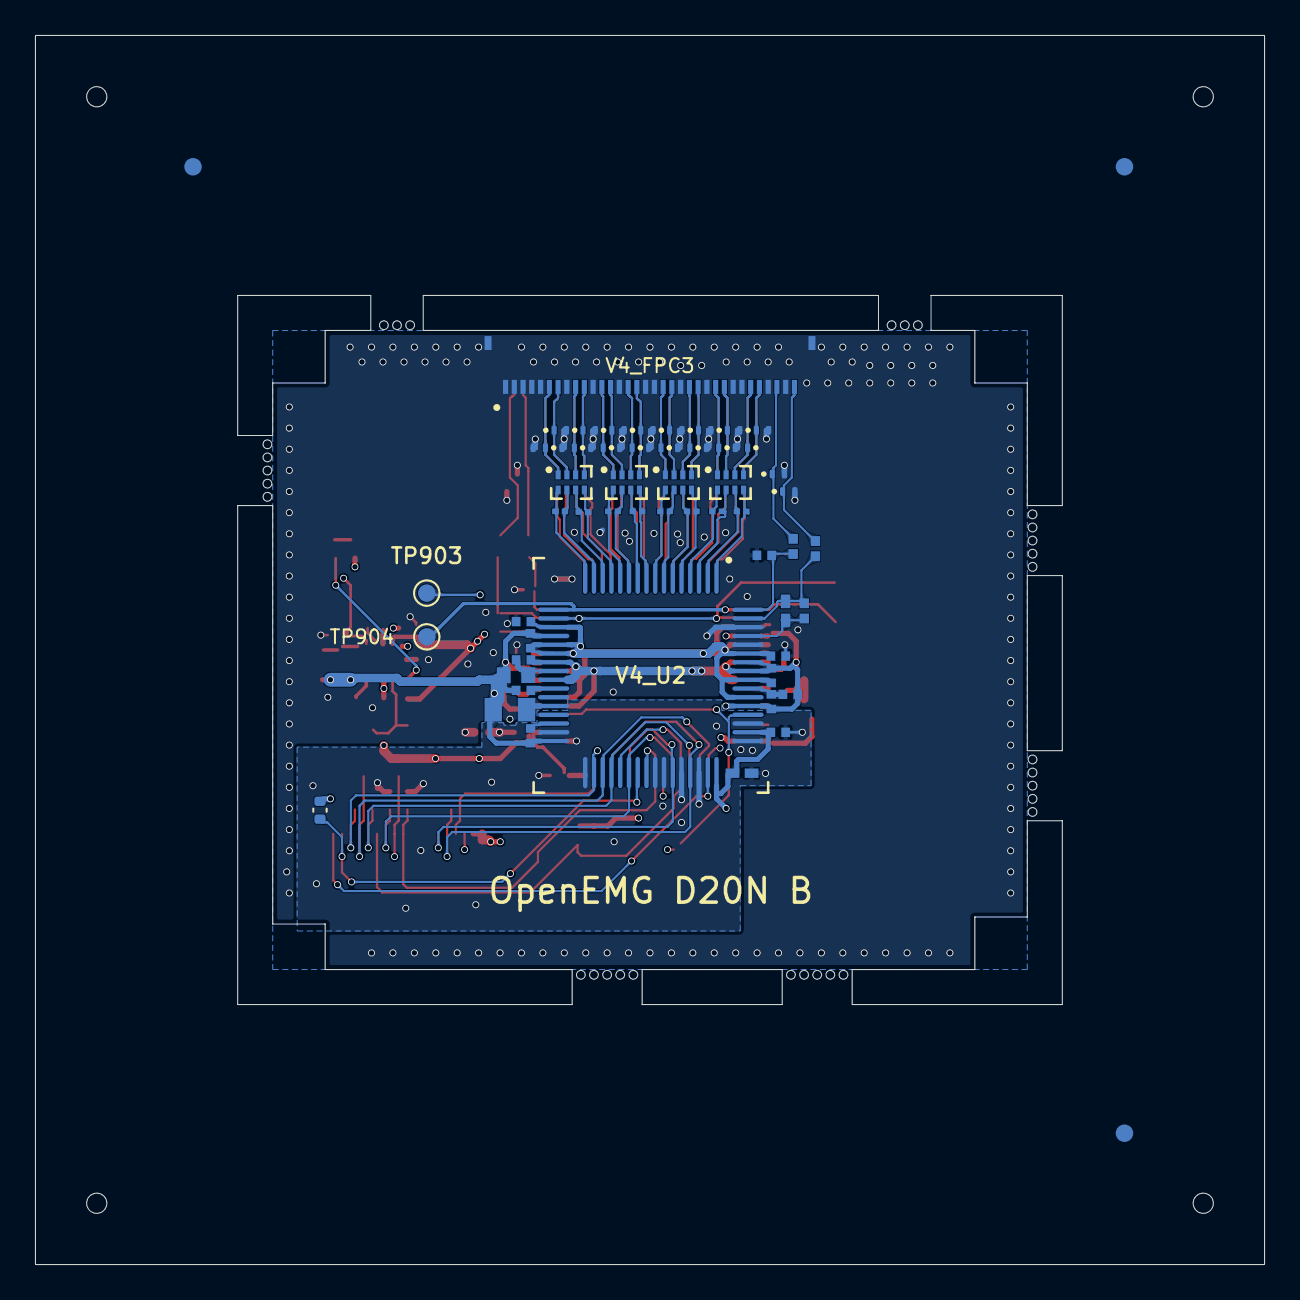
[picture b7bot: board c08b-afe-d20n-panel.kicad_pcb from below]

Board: 4 copper layers, 70.2 x 70.2 mm, 132 parts (53 on the bottom side), 111 nets.

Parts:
C901: 10uF; C901
C902: 4.7uF; C902
D901: XL-1005UGC; D901
D910: ESD401DPYR; D910
D911: ESD401DPYR; D911
D912: ESD401DPYR; D912
D913: ESD401DPYR; D913
D914: ESD401DPYR; D914
D915: ESD401DPYR; D915
D916: ESD401DPYR; D916
D917: ESD401DPYR; D917
D918: ESD401DPYR; D918
D919: ESD401DPYR; D919
D920: ESD401DPYR; D920
D921: ESD401DPYR; D921
D922: ESD401DPYR; D922
D923: ESD401DPYR; D923
D924: ESD401DPYR; D924
D925: ESD401DPYR; D925
D926: ESD401DPYR; D926
D927: ESD401DPYR; D927
D930: ESD401DPYR; D930
D931: ESD401DPYR; D931
D932: ESD401DPYR; D932
D933: ESD401DPYR; D933
D934: ESD401DPYR; D934
D935: ESD401DPYR; D935
D936: ESD401DPYR; D936
D937: ESD401DPYR; D937
D938: ESD401DPYR; D938
D939: ESD401DPYR; D939
D940: ESD401DPYR; D940
D941: ESD401DPYR; D941
D942: ESD401DPYR; D942
D943: ESD401DPYR; D943
D944: ESD401DPYR; D944
D945: ESD401DPYR; D945
D946: ESD401DPYR; D946
D947: ESD401DPYR; D947
J_AFE: FH34SRJ-20S-0.5SH(50) (LCSC C2802370); Hirose_FH34SRJ-20S-0.5SH
PANEL: rails
R801: 10k; R801
R802: 10k; R802
R803: 10k; R803
R804: 10k; R804
R805: 10k; R805
R806: 10k; R806
R807: 10k; R807
R808: 10k; R808
R901: 10kΩ; R901
TP901: V4_REF2; TP901
TP902: V4_REF1; TP902
TP903: V4_REF2; TP903
TP904: V4_REF1; TP904
V4_C31: 1uF; V4_C31
V4_C32: 100nF; V4_C32
V4_C33: 1uF; V4_C33
V4_C34: 100nF; V4_C34
V4_C35: 1uF; V4_C35
V4_C36: 100nF; V4_C36
V4_C37: 100nF; V4_C37
V4_C43: 1uF; V4_C43
V4_C44: 1uF; V4_C44
V4_C45: 100nF; V4_C45
V4_C46: 10uF; V4_C46
V4_C47: 10nF; V4_C47
V4_C48: 100nF; V4_C48
V4_C49: 1uF; V4_C49
V4_C50: 100nF; V4_C50
V4_C54: 22uF; V4_C54
V4_C72: 22pF; V4_C72
V4_C73: 22pF; V4_C73
V4_C74: 22pF; V4_C74
V4_C75: 22pF; V4_C75
V4_C76: 22pF; V4_C76
V4_C77: 22pF; V4_C77
V4_C78: 22pF; V4_C78
V4_C79: 22pF; V4_C79
V4_C81: 100nF; V4_C81
V4_C82: 100nF; V4_C82
V4_C83: 2.2uF; V4_C83
V4_C84: 2.2uF; V4_C84
V4_C85: 1uF; V4_C85
V4_C86: 1uF; V4_C86
V4_C87: 100nF; V4_C87
V4_C88: 10uF; V4_C88
V4_C89: 10nF; V4_C89
V4_C90: 100nF; V4_C90
V4_C91: 1uF; V4_C91
V4_C92: 22uF; V4_C92
V4_C109: 22pF; V4_C109
V4_C110: 22pF; V4_C110
V4_C111: 22pF; V4_C111
V4_C112: 22pF; V4_C112
V4_C113: 22pF; V4_C113
V4_C114: 22pF; V4_C114
V4_C115: 22pF; V4_C115
V4_C116: 22pF; V4_C116
V4_C117: 1uF; V4_C117
V4_C118: 100nF; V4_C118
V4_C119: 1uF; V4_C119
V4_C120: 100nF; V4_C120
V4_C121: 1uF; V4_C121
V4_C122: 100nF; V4_C122
V4_C123: 100pF; V4_C123
V4_C124: 100pF; V4_C124
V4_FPC1, V4_FPC3: FH34SRJ-34S-0.5SH(50) (LCSC C424660); Hirose_FH34SRJ-34S-0.5SH
V4_LM27762: LM27762DSSR; V4_LM27762
V4_R17: 10K; V4_R17
V4_R18: 0R; V4_R18
V4_R24: 392K; V4_R24
V4_R26: 107k; V4_R26
V4_R27: 100kΩ; V4_R27
V4_R28: 100kΩ; V4_R28
V4_R29: 104k; V4_R29
V4_R32: 392K; V4_R32
V4_R34: 392K; V4_R34
V4_R35: 10K; V4_R35
V4_R36: 392K; V4_R36
V4_R37: 10K; V4_R37
V4_U1: ADS1298IPAGR; V4_U1
V4_U2: ADS1298IPAGR; V4_U2
V4_U3: 15kΩ; V4_U3
V4_U4: 15kΩ; V4_U4
V4_U5: 15kΩ; V4_U5
V4_U6: 15kΩ; V4_U6
V4_U7: 15kΩ; V4_U7
V4_U8: 15kΩ; V4_U8
V4_U9: 15kΩ; V4_U9
V4_U10: 15kΩ; V4_U10
V4_X1: 2.048MHz; V4_X1

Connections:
3V3: C901.2, J_AFE.19, J_AFE.20, R801.2, R802.2, R901.1, V4_C31.2, V4_C32.2, V4_C37.2, V4_C81.2, V4_C82.2, V4_C117.2, V4_C118.2, V4_LM27762.3, V4_LM27762.8, V4_LM27762.12, V4_U1.48, V4_U1.50, V4_U2.48, V4_U2.50, V4_X1.1, V4_X1.4
ADS_CLKSEL: J_AFE.18, V4_R17.2, V4_U1.52, V4_U2.52
ADS_CS_A: J_AFE.10, R801.1, V4_U1.39
ADS_CS_B: J_AFE.4, R802.1, V4_U2.39
ADS_DRDY_A: J_AFE.17, V4_U1.47
ADS_DRDY_B: J_AFE.3, V4_U2.47
ADS_PWDN: J_AFE.6, R804.1, V4_U1.35, V4_U2.35
ADS_RESET: J_AFE.7, R803.1, V4_U1.36, V4_U2.36
ADS_START: J_AFE.9, R805.1, V4_U1.38, V4_U2.38
AFE_CLK_IN: J_AFE.8, V4_U1.37, V4_U2.37, V4_X1.3
AFE_GPIO3: J_AFE.16, R808.1, V4_U1.45, V4_U2.45
AGND: C901.1, C902.1, D910.2, D911.2, D912.2, D913.2, D914.2, D915.2, D916.2, D917.2, D918.2, D919.2, D920.2, D921.2, D922.2, D923.2, D924.2, D925.2, D926.2, D927.2, D930.2, D931.2, D932.2, D933.2, D934.2, D935.2, D936.2, D937.2, D938.2, D939.2, D940.2, D941.2, D942.2, D943.2, D944.2, D945.2, D946.2, D947.2, V4_C33.1, V4_C34.1, V4_C81.1, V4_C82.1, V4_C83.1, V4_C84.1, V4_C119.1, V4_C120.1, V4_C123.2, V4_C124.2, V4_FPC1.1, V4_FPC1.2, V4_FPC1.3, V4_FPC1.4, V4_FPC1.7, V4_FPC1.8, V4_FPC1.11, V4_FPC1.14, V4_FPC1.17, V4_FPC1.18, V4_FPC1.21, V4_FPC1.24, V4_FPC1.27, V4_FPC1.30, V4_FPC1.31, V4_FPC1.34, V4_FPC1.MP, V4_FPC3.1, V4_FPC3.2, V4_FPC3.3, V4_FPC3.4, V4_FPC3.5, V4_FPC3.8, V4_FPC3.11, V4_FPC3.14, V4_FPC3.17, V4_FPC3.18, V4_FPC3.21, V4_FPC3.24, V4_FPC3.27, V4_FPC3.28, V4_FPC3.31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
DIN_B: J_AFE.5, R807.1, V4_U1.34, V4_U2.34
DOUT_B: J_AFE.15, V4_U1.43, V4_U2.43
GND: J_AFE.1, J_AFE.12, J_AFE.14, J_AFE.21, J_AFE.22, R803.2, R804.2, R805.2, R806.2, R807.2, R808.2, V4_C31.1, V4_C32.1, V4_C37.1, V4_C117.1, V4_C118.1, V4_R17.1, V4_R18.1, V4_U1.31, V4_U1.33, V4_U1.41, V4_U1.42, V4_U1.44, V4_U1.46, V4_U1.49, V4_U1.51, V4_U2.31, V4_U2.33, V4_U2.41, V4_U2.42, V4_U2.44, V4_U2.46, V4_U2.49, V4_U2.51, V4_X1.2
SCLK_B: J_AFE.11, R806.1, V4_U1.40, V4_U2.40
V4_$1N19: V4_C45.2, V4_C46.1, V4_U1.24
V4_$1N24: V4_C44.2, V4_U1.26
V4_$1N25: V4_C54.2, V4_U1.28
V4_$1N26: V4_C43.2, V4_U1.30
V4_$1N44: V4_C48.2, V4_C49.1, V4_U1.55
V4_$1N307: V4_C85.2, V4_U2.30
V4_$1N308: V4_C92.2, V4_U2.28
V4_$1N309: V4_C86.2, V4_U2.26
V4_$1N319: V4_C87.2, V4_C88.1, V4_U2.24
V4_$1N323: V4_C90.2, V4_C91.1, V4_U2.55
V4_$1N350: V4_C123.1, V4_R35.1, V4_U1.64
V4_$1N353: V4_C124.1, V4_R37.1, V4_U2.64
V4_$2N83: D927.1, V4_FPC1.5, V4_U6.1
V4_$2N85: D926.1, V4_FPC1.6, V4_U6.2
V4_$2N86: D925.1, V4_FPC1.9, V4_U6.3
V4_$2N87: D924.1, V4_FPC1.10, V4_U6.4
V4_$2N90: D921.1, V4_FPC1.15, V4_U5.3
V4_$2N93: D918.1, V4_FPC1.20, V4_U4.2
V4_$2N94: D917.1, V4_FPC1.22, V4_U4.3
V4_$2N95: D916.1, V4_FPC1.23, V4_U4.4
V4_$2N96: D915.1, V4_FPC1.25, V4_U3.1
V4_$2N97: D914.1, V4_FPC1.26, V4_U3.2
V4_$2N98: D913.1, V4_FPC1.28, V4_U3.3
V4_$2N111: D919.1, V4_FPC1.19, V4_U4.1
V4_$2N118: D923.1, V4_FPC1.12, V4_U5.1
V4_$2N119: D922.1, V4_FPC1.13, V4_U5.2
V4_$2N120: D920.1, V4_FPC1.16, V4_U5.4
V4_$2N121: D912.1, V4_FPC1.29, V4_U3.4
V4_$2N324: D932.1, V4_FPC3.30, V4_U7.4
V4_$2N325: D940.1, V4_FPC3.16, V4_U9.4
V4_$2N326: D942.1, V4_FPC3.13, V4_U9.2
V4_$2N327: D943.1, V4_FPC3.12, V4_U9.1
V4_$2N330: D939.1, V4_FPC3.19, V4_U8.1
V4_$2N331: D933.1, V4_FPC3.29, V4_U7.3
V4_$2N332: D934.1, V4_FPC3.26, V4_U7.2
V4_$2N333: D935.1, V4_FPC3.25, V4_U7.1
V4_$2N334: D936.1, V4_FPC3.23, V4_U8.4
V4_$2N335: D937.1, V4_FPC3.22, V4_U8.3
V4_$2N336: D938.1, V4_FPC3.20, V4_U8.2
V4_$2N337: D941.1, V4_FPC3.15, V4_U9.3
V4_$2N338: D944.1, V4_FPC3.10, V4_U10.4
V4_$2N339: D945.1, V4_FPC3.9, V4_U10.3
V4_$2N340: D946.1, V4_FPC3.7, V4_U10.2
V4_$2N341: D947.1, V4_FPC3.6, V4_U10.1
V4_$3N49: D901.2, R901.2
V4_$3N56: V4_LM27762.2, V4_R26.1, V4_R27.2
V4_$3N57: V4_C50.1, V4_LM27762.9
V4_$3N58: V4_C50.2, V4_LM27762.10
V4_$3N60: V4_LM27762.7, V4_R28.1, V4_R29.2
V4_$3N62: C902.2, V4_LM27762.5
V4_+2.5V: V4_C33.2, V4_C34.2, V4_C35.2, V4_C36.2, V4_C83.2, V4_C119.2, V4_C120.2, V4_C121.2, V4_C122.2, V4_LM27762.11, V4_R26.2, V4_U1.19, V4_U1.21, V4_U1.22, V4_U1.54, V4_U1.56, V4_U1.59, V4_U2.19, V4_U2.21, V4_U2.22, V4_U2.54, V4_U2.56, V4_U2.59
V4_-2.5V: V4_C35.1, V4_C36.1, V4_C43.1, V4_C44.1, V4_C45.1, V4_C46.2, V4_C48.1, V4_C49.2, V4_C54.1, V4_C84.2, V4_C85.1, V4_C86.1, V4_C87.1, V4_C88.2, V4_C90.1, V4_C91.2, V4_C92.1, V4_C121.1, V4_C122.1, V4_LM27762.6, V4_R29.1, V4_U1.20, V4_U1.23, V4_U1.25, V4_U1.32, V4_U1.53, V4_U1.57, V4_U1.58, V4_U2.20, V4_U2.23, V4_U2.25, V4_U2.32, V4_U2.53, V4_U2.57, V4_U2.58
V4_BIASINV1: V4_C47.1, V4_R24.1, V4_U1.61
V4_BIASINV12: V4_C89.1, V4_R32.1, V4_U2.61
V4_BIASOUT1: V4_C47.2, V4_R24.2, V4_R34.1, V4_U1.63
V4_BIASOUT12: V4_C89.2, V4_R32.2, V4_R36.1, V4_U2.63
V4_BIAS_DRV1: D910.1, V4_FPC1.33, V4_R34.2
V4_IN1N: V4_C72.1, V4_U1.15, V4_U6.7
V4_IN1N2: V4_C109.1, V4_U2.15, V4_U10.7
V4_IN1P: V4_C72.2, V4_U1.16, V4_U6.8
V4_IN1P2: V4_C109.2, V4_U2.16, V4_U10.8
V4_IN2N: V4_C73.1, V4_U1.13, V4_U6.5
V4_IN2N2: V4_C110.1, V4_U2.13, V4_U10.5
V4_IN2P: V4_C73.2, V4_U1.14, V4_U6.6
V4_IN2P2: V4_C110.2, V4_U2.14, V4_U10.6
V4_IN3N: V4_C74.1, V4_U1.11, V4_U5.7
V4_IN3N2: V4_C111.1, V4_U2.11, V4_U9.7
V4_IN3P: V4_C74.2, V4_U1.12, V4_U5.8
V4_IN3P2: V4_C111.2, V4_U2.12, V4_U9.8
V4_IN4N: V4_C75.1, V4_U1.9, V4_U5.5
V4_IN4N2: V4_C112.1, V4_U2.9, V4_U9.5
V4_IN4P: V4_C75.2, V4_U1.10, V4_U5.6
V4_IN4P2: V4_C112.2, V4_U2.10, V4_U9.6
V4_IN5N: V4_C76.1, V4_U1.7, V4_U4.7
V4_IN5N2: V4_C113.1, V4_U2.7, V4_U8.7
V4_IN5P: V4_C76.2, V4_U1.8, V4_U4.8
V4_IN5P2: V4_C113.2, V4_U2.8, V4_U8.8
V4_IN6N: V4_C77.1, V4_U1.5, V4_U4.5
V4_IN6N2: V4_C114.1, V4_U2.5, V4_U8.5
V4_IN6P: V4_C77.2, V4_U1.6, V4_U4.6
V4_IN6P2: V4_C114.2, V4_U2.6, V4_U8.6
V4_IN7N: V4_C78.1, V4_U1.3, V4_U3.7
V4_IN7N2: V4_C115.1, V4_U2.3, V4_U7.7
V4_IN7P: V4_C78.2, V4_U1.4, V4_U3.8
V4_IN7P2: V4_C115.2, V4_U2.4, V4_U7.8
V4_IN8N: V4_C79.1, V4_U1.1, V4_U3.5
V4_IN8N2: V4_C116.1, V4_U2.1, V4_U7.5
V4_IN8P: V4_C79.2, V4_U1.2, V4_U3.6
V4_IN8P2: V4_C116.2, V4_U2.2, V4_U7.6
V4_POWERGOOD: D901.1, V4_LM27762.1
V4_REF1: TP902.1, TP904.1, V4_U1.17, V4_U2.17
V4_REF2: TP901.1, TP903.1, V4_U1.18, V4_U2.18
V4_RLD_OUT2: D930.1, V4_FPC3.34, V4_R36.2
V4_WCT: D911.1, V4_FPC1.32, V4_R35.2
V4_WCT2: D931.1, V4_FPC3.32, V4_R37.2
